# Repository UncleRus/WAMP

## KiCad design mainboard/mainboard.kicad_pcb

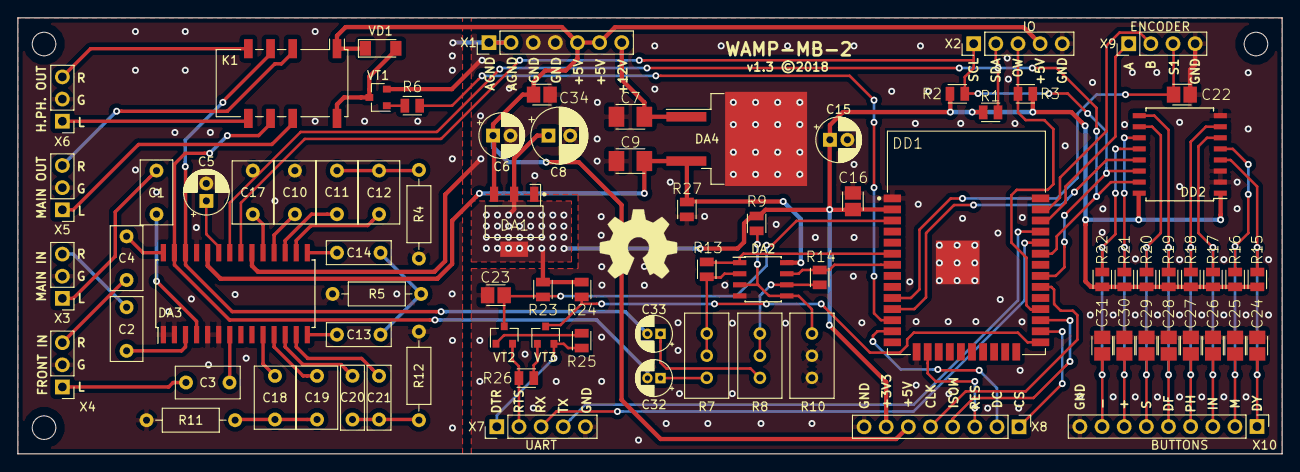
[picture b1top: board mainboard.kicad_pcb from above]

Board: 2 copper layers, 145.0 x 50.0 mm, 82 parts (0 on the bottom side), 73 nets.

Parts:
C1, C2, C3, C4: 470n; C_Rect_L7.2mm_W3.5mm_P5.00mm_FKS2_FKP2_MKS2_MKP2
C5, C6: 10uF; CP_Radial_D5.0mm_P2.00mm
C7: 330n; CAPC3216X180N
C8: 100uF; CP_Radial_D6.3mm_P2.50mm
C9: 100n; CAPC3216X180N
C10, C17: 5n6; C_Rect_L7.0mm_W4.5mm_P5.00mm
C11, C18: 18n; C_Rect_L7.0mm_W4.5mm_P5.00mm
C12, C19: 22n; C_Rect_L7.0mm_W4.5mm_P5.00mm
C13, C14, C20, C21: 100n; C_Rect_L7.2mm_W2.5mm_P5.00mm_FKS2_FKP2_MKS2_MKP2
C15: 22uF; CP_Radial_D5.0mm_P2.00mm
C16, C22, C23, C24, C25, C26, C27, C28, C29, C30, C31, C34: 100n; CAPC2013X140N
C32, C33: 1uF; CP_Radial_D4.0mm_P1.50mm
DA1: LD1117S33; SOT230P700X180-4N
DA2: LM358DT; SOIC-8_3.9x4.9mm_P1.27mm
DA3: TDA7439DS; SOIC-28W_7.5x17.9mm_P1.27mm
DA4: L7809P; TO-263-2
DD1: ESP32-WROOM-32; ESPRESSIF_ESP32-WROOM-32
DD2: PCF8574T; SOIC-16W_7.5x10.3mm_P1.27mm
K1: G6S-2F-5DC; Relay_DPDT_Omron_G6S-2F
R1, R2, R24: 4k7; RESC2013X65N
R3, R6, R15, R16, R17, R18, R19, R20, R21, R22, R23, R25, R26: 10k; RESC2013X65N
R4, R11: 2k7; R_Axial_DIN0207_L6.3mm_D2.5mm_P10.16mm_Horizontal
R5, R12: 5k6; R_Axial_DIN0207_L6.3mm_D2.5mm_P10.16mm_Horizontal
R7, R8: 200k; Potentiometer_Bourns_3296W_Vertical
R9: 100k; RESC2013X65N
R10: 50k; Potentiometer_Bourns_3296W_Vertical
R13, R14: 50k; RESC2013X65N
R27: 3k3; RESC2013X65N
VD1: 1N4148; D_MiniMELF
VT1, VT2, VT3: MMBT3904; SOT-23
X1: POWER; PinHeader_1x07_P2.54mm_Vertical
X2: IO; PinHeader_1x05_P2.54mm_Vertical
X3: INPUT; PinHeader_1x03_P2.54mm_Vertical
X4: FRONT INPUT; PinHeader_1x03_P2.54mm_Vertical
X5: MAIN OUTPUT; PinHeader_1x03_P2.54mm_Vertical
X6: PHONES OUTPUT; PinHeader_1x03_P2.54mm_Vertical
X7: UART; PinHeader_1x05_P2.54mm_Vertical
X8: DISPLAY; PinHeader_1x08_P2.54mm_Vertical
X9: ENCODER; PinHeader_1x04_P2.54mm_Vertical
X10: BUTTONS; PinHeader_1x09_P2.54mm_Vertical

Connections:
+3V3: C8.1, C15.1, C16.1, DA1.2, DA1.4, DD1.2, DD2.1, DD2.16, R1.1, R2.1, R3.1, R9.1, R15.1, R16.1, R17.1, R18.1, R19.1, R20.1, R21.1, R22.1, R23.1, R24.1, X8.7
+5V: C6.1, C34.1, DA1.3, K1.1, VD1.1, X1.5, X1.6, X2.4, X8.6
+9V: C9.1, DA2.8, DA3.24, DA4.3, R27.1
/12V: C7.1, DA4.1, X1.7
/ADC6: DA2.1, DD1.6, R13.2
/ADC7: DA2.7, DD1.7, R14.1
/BINT: DD1.11, DD2.13
/BIN_L: C13.2, DA3.14
/BIN_R: C20.2, DA3.12
/BOUT_L: C14.2, DA3.15
/BOUT_R: C21.2, DA3.13
/B_DEFEAT: C28.1, DD2.9, R19.2, X10.5
/B_DISPLAY: C24.1, DD2.4, R15.2, X10.1
/B_INPUT: C26.1, DD2.6, R17.2, X10.3
/B_MINUS: C31.1, DD2.12, R22.2, X10.8
/B_MUTE: C25.1, DD2.5, R16.2, X10.2
/B_PHONES: C27.1, DD2.7, R18.2, X10.4
/B_PLUS: C30.1, DD2.11, R21.2, X10.7
/B_SETTINGS: C29.1, DD2.10, R20.2, X10.6
/CS0: DD1.26, X8.1
/DC: DD1.13, X8.2
/EN: C23.1, DD1.3, R23.2, VT2.3
/IO0: DD1.25, R24.2, VT3.3
/LOUT: C32.2, DA3.27, K1.7
/MIN_L: C11.2, DA3.17
/MIN_R: C18.2, DA3.10
/MOSI: DD1.27, X8.4
/MOUT_L: C12.2, DA3.16
/MOUT_R: C19.2, DA3.11
/ONEWIRE: DD1.28, R3.2, X2.3
/PH_SW: DD1.12, R6.2
/RES: DD1.16, X8.3
/RE_A: DD1.36, X9.1
/RE_B: DD1.37, X9.2
/RE_BTN: C22.1, DD1.10, X9.3
/ROUT: C33.2, DA3.26, K1.4
/RXD: DD1.34, X7.3
/SCL: DA3.21, DD1.31, DD2.14, R2.2, X2.1
/SCLK: DD1.30, X8.5
/SDA: DA3.22, DD1.33, DD2.15, R1.2, X2.2
/TREB_L: C10.2, DA3.18
/TREB_R: C17.2, DA3.19
/TXD: DD1.35, X7.4
AGND: C5.2, C10.1, C17.1, DA3.1, DA3.2, DA3.5, DA3.6, DA3.25, R4.1, R5.1, R11.2, R12.2, X1.1, X1.2, X3.2, X4.2, X5.2, X6.2
GND: C6.2, C7.2, C8.2, C9.2, C15.2, C16.2, C22.2, C23.2, C24.2, C25.2, C26.2, C27.2, C28.2, C29.2, C30.2, C31.2, C34.2, DA1.1, DA2.4, DA3.20, DA4.2, DD1.1, DD1.15, DD1.38, DD1.39, DD2.2, DD2.3, DD2.8, R10.2, R10.3, R27.2, VT1.2, X1.3, X1.4, X2.5, X7.5, X8.8, X9.4, X10.9
unnamed: C1.1, X3.1
unnamed: C1.2, DA3.4
unnamed: C2.1, X3.3
unnamed: C2.2, DA3.3
unnamed: C3.1, X4.1
unnamed: C3.2, DA3.7
unnamed: C4.1, X4.3
unnamed: C4.2, DA3.28
unnamed: C5.1, DA3.23
unnamed: C11.1, C12.1, R4.2
unnamed: C13.1, C14.1, R5.2
unnamed: C18.1, C19.1, R11.1
unnamed: C20.1, C21.1, R12.1
unnamed: C32.1, R7.1
unnamed: C33.1, R8.1
unnamed: DA2.2, R7.2, R7.3, R13.1
unnamed: DA2.3, DA2.5, R9.2, R10.1
unnamed: DA2.6, R8.2, R8.3, R14.2
unnamed: K1.3, X5.3
unnamed: K1.5, X6.3
unnamed: K1.6, X6.1
unnamed: K1.8, X5.1
unnamed: K1.10, VD1.2, VT1.3
unnamed: R6.1, VT1.1
unnamed: R25.1, VT2.1
unnamed: R25.2, VT3.2, X7.1
unnamed: R26.1, VT3.1
unnamed: R26.2, VT2.2, X7.2

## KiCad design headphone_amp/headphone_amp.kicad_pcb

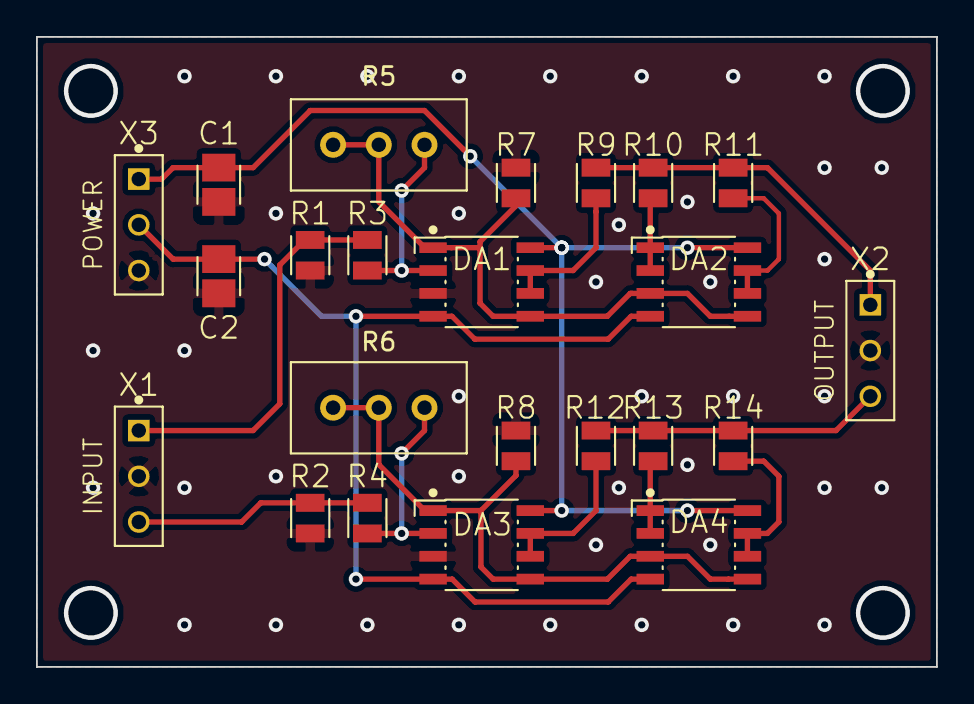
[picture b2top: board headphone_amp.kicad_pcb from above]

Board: 2 copper layers, 50.0 x 35.0 mm, 23 parts (0 on the bottom side), 17 nets.

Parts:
C1, C2: 100n; CAPC2013X140N
DA1, DA2, DA3, DA4: NE5532AD; SOIC127P600X175-8N
R1, R2: 100k; RESC2013X65N
R3, R4, R7, R8: 10k; RESC2013X65N
R5, R6: 100k; Potentiometer_Bourns_3296W_Vertical
R9, R10, R11, R12, R13, R14: 300; RESC2013X65N
X1: INPUT; CON_CONN_BL_03X01
X2: OUTPUT; CON_CONN_BL_03X01
X3: POWER; CON_CONN_BL_03X01

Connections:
+15V: C1.1, DA1.8, DA2.8, DA3.8, DA4.8, X3.1
-15V: C2.1, DA1.4, DA2.4, DA3.4, DA4.4, X3.2
AGND: C1.2, C2.2, DA1.3, DA3.3, R1.1, R2.1, R7.1, R8.1, X1.2, X2.2, X3.3
unnamed: DA1.1, DA1.5, DA2.3, DA2.5, R5.2, R5.3, R7.2
unnamed: DA1.2, R3.2, R5.1
unnamed: DA1.6, DA1.7, R9.1
unnamed: DA2.1, DA2.2, R10.1
unnamed: DA2.6, DA2.7, R11.1
unnamed: DA3.1, DA3.5, DA4.3, DA4.5, R6.2, R6.3, R8.2
unnamed: DA3.2, R4.2, R6.1
unnamed: DA3.6, DA3.7, R12.1
unnamed: DA4.1, DA4.2, R13.1
unnamed: DA4.6, DA4.7, R14.1
unnamed: R1.2, R3.1, X1.1
unnamed: R2.2, R4.1, X1.3
unnamed: R9.2, R10.2, R11.2, X2.1
unnamed: R12.2, R13.2, R14.2, X2.3

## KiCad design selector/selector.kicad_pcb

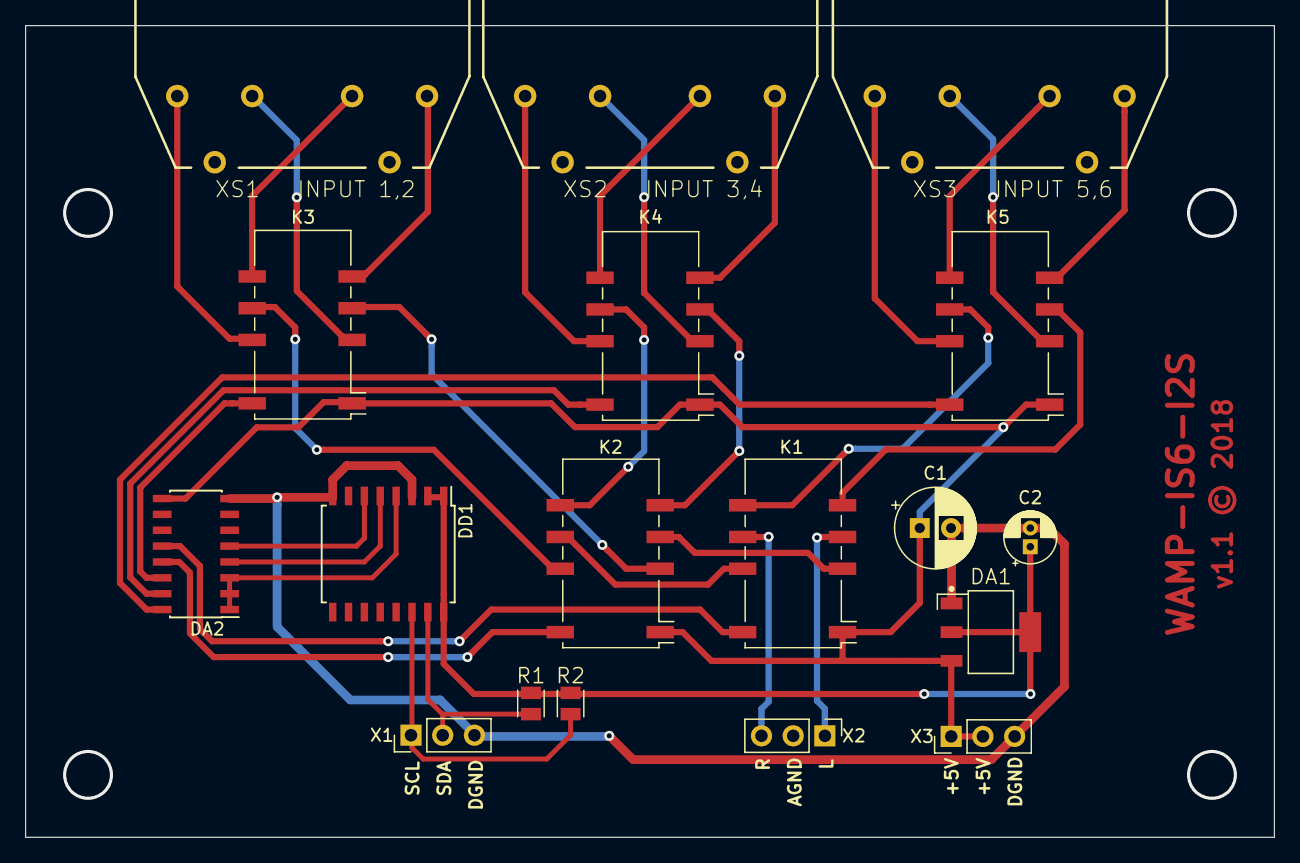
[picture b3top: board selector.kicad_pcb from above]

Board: 2 copper layers, 100.0 x 65.0 mm, 18 parts (0 on the bottom side), 36 nets.

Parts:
C1: 220uF; CP_Radial_D6.3mm_P2.50mm
C2: 10uF; CP_Radial_D4.0mm_P1.50mm
DA1: LD1117S33; SOT230P700X180-4N
DA2: ULN2003AD; SOIC-16_3.9x9.9mm_P1.27mm
DD1: PCF8574T; SOIC-16W_7.5x10.3mm_P1.27mm
K1, K2, K3, K4, K5: G6S-2F-5DC; Relay_DPDT_Omron_G6S-2F
R1, R2: 10k; RESC2013X65N
X1: I2C; PinHeader_1x03_P2.54mm_Vertical
X2: OUTPUT; PinHeader_1x03_P2.54mm_Vertical
X3: POWER; PinHeader_1x03_P2.54mm_Vertical
XS1: INPUT 1,2; con-amphenol-RCA-4-117-01
XS2: INPUT 3,4; con-amphenol-RCA-4-117-01
XS3: INPUT 5,6; con-amphenol-RCA-4-117-01

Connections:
+3V3: C2.1, DA1.2, DA1.4, DD1.1, DD1.2, DD1.16, R1.1, R2.1
+5V: C1.1, DA1.3, DA2.9, K1.1, K2.1, K3.1, K4.1, K5.1, X3.1, X3.2
/IN1_L: K3.3, XS1.1
/IN1_R: K3.8, XS1.2
/IN2_L: K3.5, XS1.4
/IN2_R: K3.6, XS1.5
/IN3_L: K4.3, XS2.1
/IN3_R: K4.8, XS2.2
/IN4_L: K4.5, XS2.4
/IN4_R: K4.6, XS2.5
/IN5_L: K5.3, XS3.1
/IN5_R: K5.8, XS3.2
/IN6_L: K5.5, XS3.4
/IN6_R: K5.6, XS3.5
/IN_0A: DA2.16, K5.10
/IN_0B: DA2.15, K4.10
/IN_0C: DA2.14, K3.10
/IN_1: DA2.13, K2.10
/IN_2: DA2.12, K1.10
AGND: X2.2, XS1.3, XS1.6, XS2.3, XS2.6, XS3.3, XS3.6
GND: C1.2, C2.2, DA1.1, DA2.8, DD1.3, DD1.8, X1.3, X3.3
unnamed: DA2.1, DA2.2, DA2.3, DD1.4
unnamed: DA2.4, DD1.5
unnamed: DA2.5, DD1.6
unnamed: DD1.14, R2.2, X1.1
unnamed: DD1.15, R1.2, X1.2
unnamed: K1.3, K2.4
unnamed: K1.4, X2.1
unnamed: K1.5, K5.4
unnamed: K1.6, K5.7
unnamed: K1.7, X2.3
unnamed: K1.8, K2.7
unnamed: K2.3, K3.4
unnamed: K2.5, K4.4
unnamed: K2.6, K4.7
unnamed: K2.8, K3.7

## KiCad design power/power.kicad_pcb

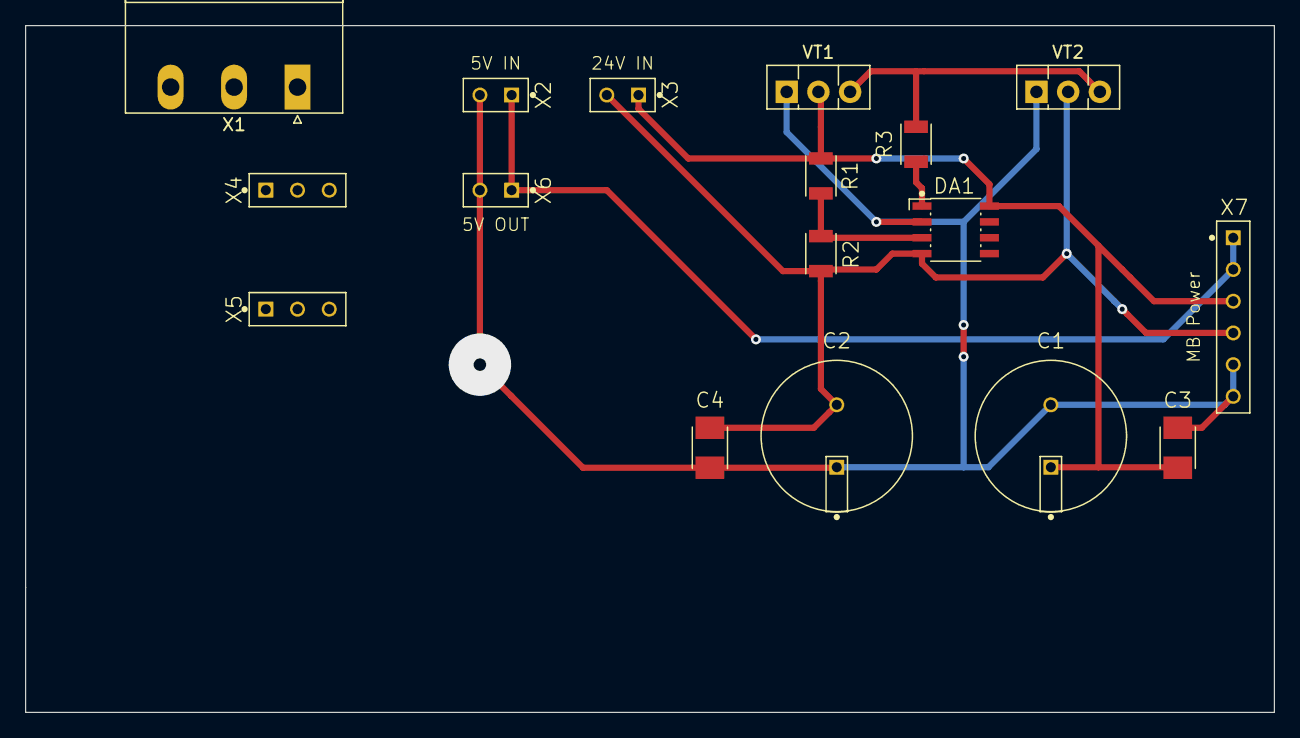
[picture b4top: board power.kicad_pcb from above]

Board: 2 copper layers, 100.0 x 55.0 mm, 17 parts (0 on the bottom side), 9 nets.

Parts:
C1, C2: 2200uF; CAPPRD500W60D1200H2700N
C3, C4: 220n; CAPC3216X180N
DA1: LM393M; SOIC127P600X175-8N
R1, R2: 10k; RESC3115X65N
R3: 1k; RESC3115X65N
VT1: BD135; TO-126-3_Vertical
VT2: BD136; TO-126-3_Vertical
X1: PA IN; PhoenixContact_MSTBA_2,5_3-G-5,08_1x03_P5.08mm_Horizontal
X2: 5V IN; CON_CONN_BL_02X01
X3: 24V IN; CON_CONN_BL_02X01
X4: PA OUT1; CON_CONN_BL_03X01
X5: PA OU2; CON_CONN_BL_03X01
X6: 5V OUT; CON_CONN_BL_02X01
X7: MB Power; CON_CONN_BL_06X01

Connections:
/+5V: X2.1, X6.1, X7.1, X7.2
/+12V: C1.1, C3.1, DA1.8, R1.1, VT1.2, X3.1, X7.3
/+58V: X1.1, X4.1, X5.1
/-12V: C2.2, C4.2, DA1.4, R2.2, VT2.2, X3.2, X7.4
/-58V: X1.3, X4.3, X5.3
GND: C1.2, C2.1, C3.2, C4.1, DA1.2, VT1.1, VT2.1, X1.2, X2.2, X4.2, X5.2, X6.2, X7.5, X7.6
unnamed: DA1.1, R3.1
unnamed: DA1.3, R1.2, R2.1
unnamed: R3.2, VT1.3, VT2.3

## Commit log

2018-09-12 Initial upload
2018-09-12 Schematics for input selector in PDF
2018-09-12 Input selector project
2018-09-12 Fixed selector PCB, relays on different ULN2003 lines, mainboard pcb
2018-09-15 Simpler mainboard
2018-09-15 mainboard pdf
2018-09-15 gitignore updated
2018-09-21 Film caps on MB, new powering scheme, opamp replaced
2018-09-21 Pad to mask clearance removed
2018-09-22 MB fixes
2018-09-22 Removed trash files
2018-09-22 Potentiometers to MB ADC module
2018-09-23 Added blocking caps to ADC input
2018-09-24 MB 7809 pinout fixed
2018-10-02 Headphone amp added, minor MB fixes
2018-10-17 v1.3
2018-11-02 Firmware started
2018-11-04 Keyboard module in firmware

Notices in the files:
mainboard/mainboard.kicad_pcb:
v1.3 ©2018
selector/selector.kicad_pcb:
v1.1 © 2018
